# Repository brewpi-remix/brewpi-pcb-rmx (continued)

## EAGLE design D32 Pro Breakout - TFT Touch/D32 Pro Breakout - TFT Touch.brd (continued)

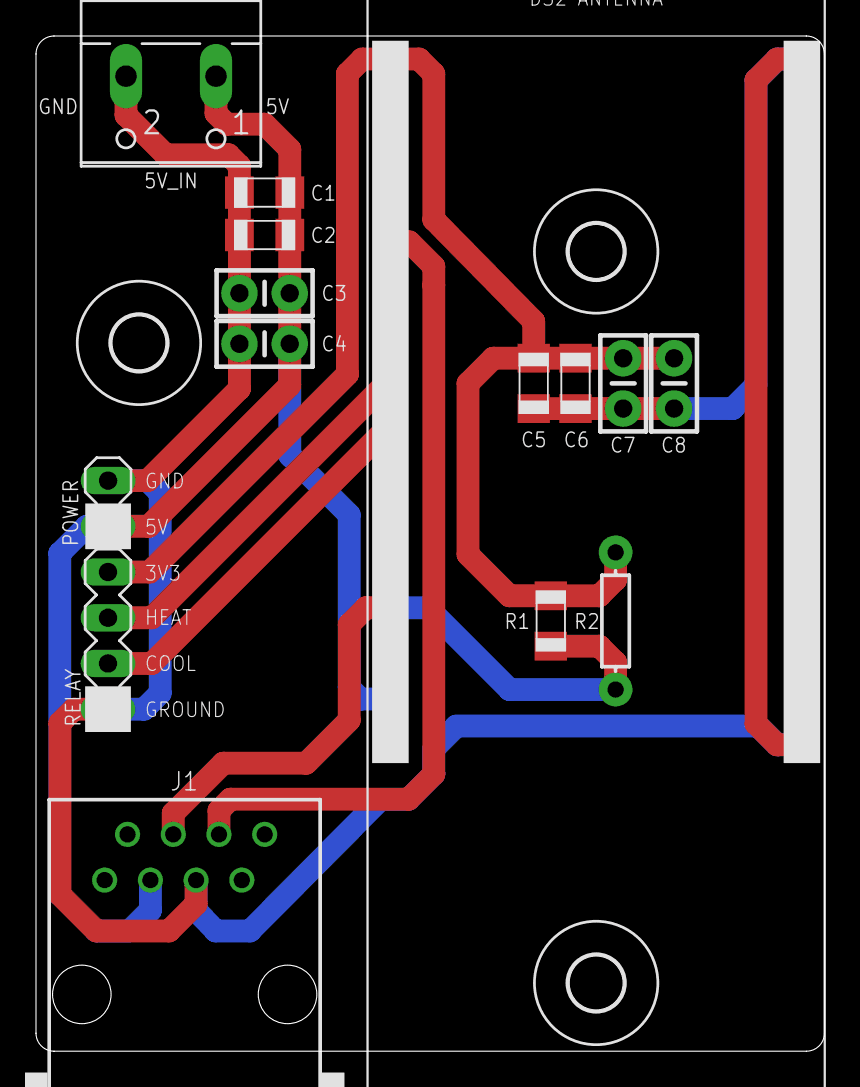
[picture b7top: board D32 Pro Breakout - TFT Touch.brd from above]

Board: 2 copper layers, 43.8 x 56.4 mm, 19 parts (1 on the bottom side), 7 nets.

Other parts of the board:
U$1, U$2, U$4: 3,0

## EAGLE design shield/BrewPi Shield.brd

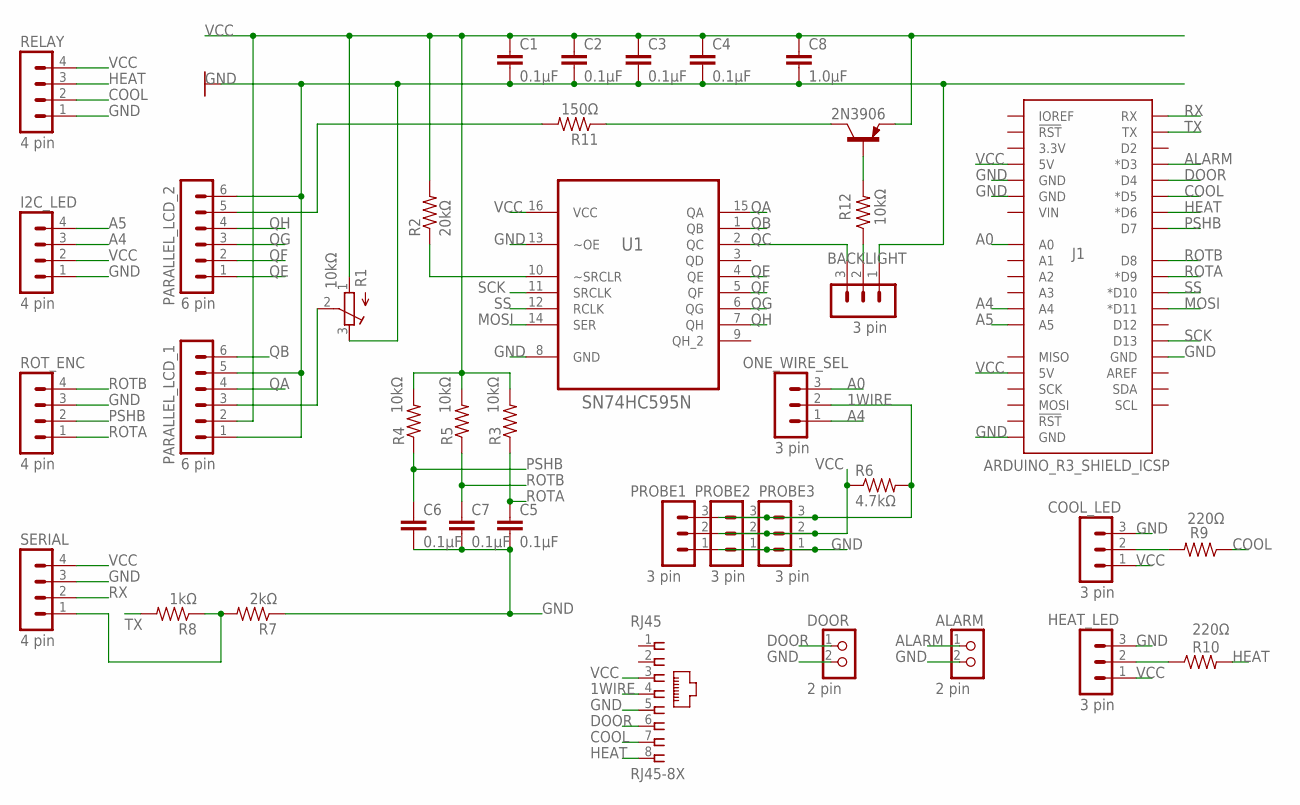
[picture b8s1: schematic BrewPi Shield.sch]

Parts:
ALARM: 2 pin; HEADER02-1
BACKLIGHT: 3 pin; HEADER03-1
C1, C2, C3, C4, C5, C6, C7: 0.1μF; CAP-PTH-SMALL-KIT
C8: 1.0μF; CAP-PTH-SMALL-KIT
COOL_LED: 3 pin; HEADER03-1
DOOR: 2 pin; HEADER02-1
HEAT_LED: 3 pin; HEADER03-1
I2C_LED: 4 pin; HEADER04-1
J1: ARDUINO_R3_SHIELD_ICSP; UNO_R3_SHIELD_ICSP
ONE_WIRE_SEL: 3 pin; HEADER03-1
PARALLEL_LCD_1, PARALLEL_LCD_2: 6 pin; HEADER06-1
PROBE1, PROBE2, PROBE3: 3 pin; HEADER03-1
Q1: 2N3906; TO92
R1: 10kΩ; RTRIM3296Y
R2: 20kΩ; AXIAL-0.3
R3, R4, R5, R12: 10kΩ; AXIAL-0.3
R6: 4.7kΩ; AXIAL-0.3
R7: 2kΩ; AXIAL-0.3
R8: 1kΩ; AXIAL-0.3
R9, R10: 220Ω; AXIAL-0.3
R11: 150Ω; AXIAL-0.3
RELAY: 4 pin; HEADER04-1
RJ45: RJ45-8X; RJ45-NO-SHIELD
ROT_ENC: 4 pin; HEADER04-1
SERIAL: 4 pin; HEADER04-1
U1: SN74HC595N; DIP254P762X508-16

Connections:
1WIRE: ONE_WIRE_SEL.2, PROBE1.3, PROBE2.3, PROBE3.3, R6.P$2 (2), RJ45.4
A0: J1.A0, ONE_WIRE_SEL.3
A4: I2C_LED.3, J1.A4, ONE_WIRE_SEL.1
A5: I2C_LED.4, J1.A5
ALARM: ALARM.1, J1.D3 (*D3)
COOL: J1.D5 (*D5), R9.P$1 (1), RELAY.2, RJ45.7
DOOR: DOOR.1, J1.D4, RJ45.6
GND: ALARM.2, BACKLIGHT.1, C1.2, C2.2, C3.2, C4.2, C5.2, C6.2, C7.2, C8.2, COOL_LED.3, DOOR.2, HEAT_LED.3, I2C_LED.1, J1.GND@0 (GND), J1.GND@1 (GND), J1.GND@2 (GND), J1.GND_ICSP (GND), PARALLEL_LCD_1.1, PARALLEL_LCD_1.5, PARALLEL_LCD_2.6, PROBE1.1, PROBE2.1, PROBE3.1, R1.3 (E), R7.P$1 (1), RELAY.1, RJ45.5, ROT_ENC.3, SERIAL.3, U1.8 (GND), U1.13 (~OE)
HEAT: J1.D6 (*D6), R10.P$2 (2), RELAY.3, RJ45.8
MOSI: J1.D11 (*D11), U1.14 (SER)
unnamed: R2.P$1 (1), U1.10 (~SRCLR)
unnamed: BACKLIGHT.2, R12.P$1 (1)
unnamed: R7.P$2 (2), R8.P$1 (1), SERIAL.1
unnamed: COOL_LED.2, R9.P$2 (2)
unnamed: PARALLEL_LCD_2.5, R11.P$2 (2)
unnamed: PARALLEL_LCD_1.3, R1.2 (S)
unnamed: Q1.1 (C), R11.P$1 (1)
unnamed: HEAT_LED.2, R10.P$1 (1)
unnamed: Q1.2 (B), R12.P$2 (2)
PSHB: C6.1, J1.D7, R4.P$1 (1), ROT_ENC.2
QA: PARALLEL_LCD_1.4, U1.15 (QA)
QB: PARALLEL_LCD_1.6, U1.1 (QB)
QC: BACKLIGHT.3, U1.2 (QC)
QE: PARALLEL_LCD_2.1, U1.4 (QE)
QF: PARALLEL_LCD_2.2, U1.5 (QF)
QG: PARALLEL_LCD_2.3, U1.6 (QG)
QH: PARALLEL_LCD_2.4, U1.7 (QH)
ROTA: C5.1, J1.D9 (*D9), R3.P$1 (1), ROT_ENC.1
ROTB: C7.1, J1.D8, R5.P$1 (1), ROT_ENC.4
RX: J1.RX, SERIAL.2
SCK: J1.D13, U1.11 (SRCLK)
SS: J1.D10 (*D10), U1.12 (RCLK)
TX: J1.TX, R8.P$2 (2)
VCC: C1.1, C2.1, C3.1, C4.1, C8.1, COOL_LED.1, HEAT_LED.1, I2C_LED.2, J1.5V, J1.5V_ICSP (5V), PARALLEL_LCD_1.2, PROBE1.2, PROBE2.2, PROBE3.2, Q1.3 (E), R1.1 (A), R2.P$2 (2), R3.P$2 (2), R4.P$2 (2), R5.P$2 (2), R6.P$1 (1), RELAY.4, RJ45.3, SERIAL.4, U1.16 (VCC)

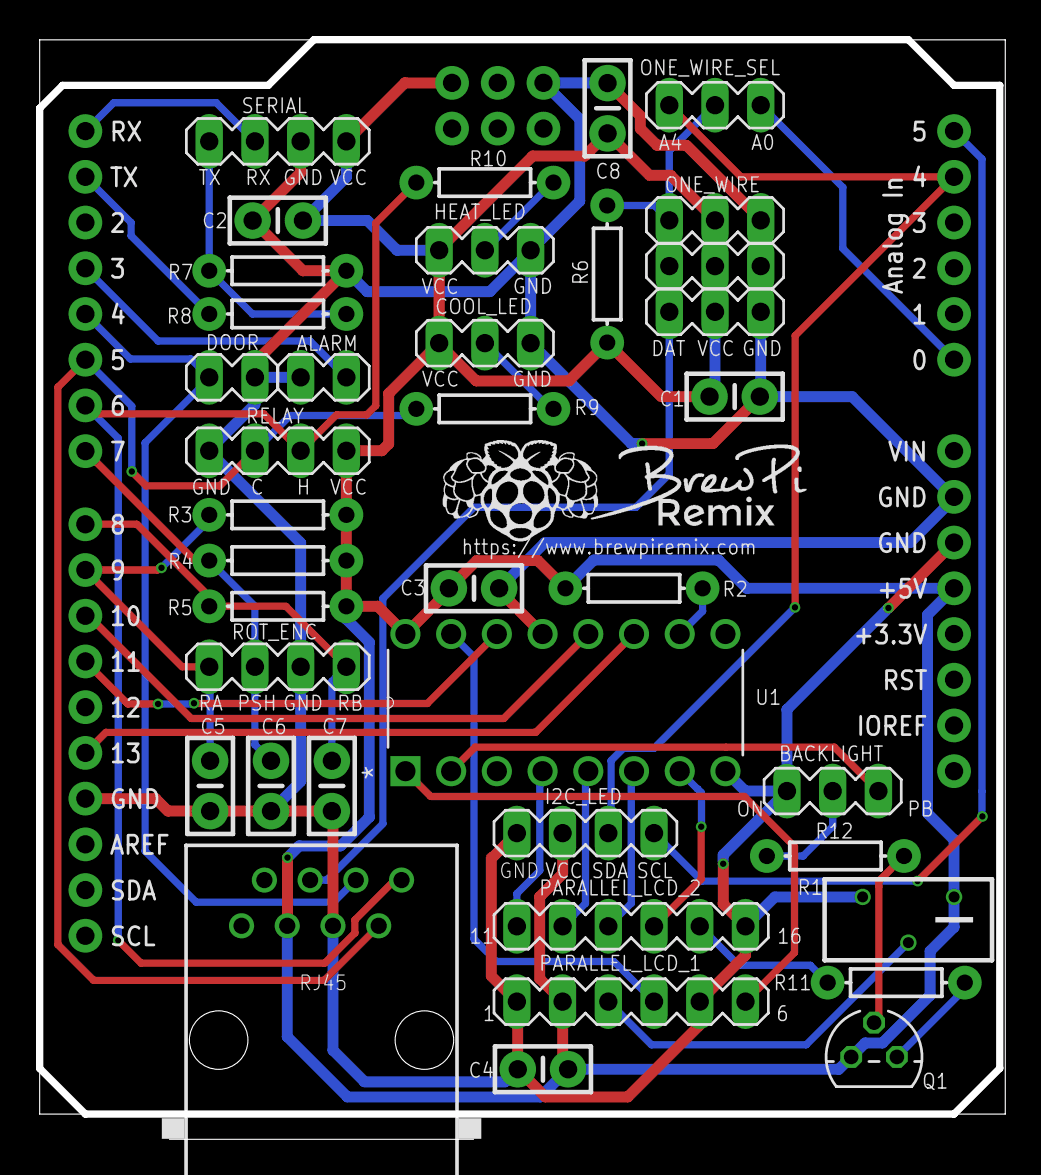
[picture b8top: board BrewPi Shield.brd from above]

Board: 2 copper layers, 53.6 x 61.1 mm, 39 parts (0 on the bottom side), 34 nets.

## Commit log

2019-06-23 Legacy 1.1 boards
2019-06-23 Updated included files
2019-06-23 Rename to versionless names
2019-06-23 Rename shield directory
2019-06-23 Added CHANGELOG
2019-06-23 Version 1.2 upload
2019-06-23 Initial upload
2019-06-23 Version 1.3 upload
2019-06-23 Version 1.3.1 upload
2019-06-23 Moved traces and silkscreens
2019-06-30 Update logo
2019-06-30 Update logo, remove acid trap
2019-06-30 Update CHANGELOGs
2019-06-30 Add labels for LEDs
2019-06-30 Update links
2019-06-30 Add README
2019-06-30 Add images
2019-06-30 Reduce image size
2019-11-10 Add ESP8266 shield
2019-11-18 Remove 90deg connection at power
2019-11-18 Update link and images
2019-11-18 Change to pcbs.io link
2019-11-18 Fix typo
2019-11-18 Update to pcbs.io images
2019-11-18 Change all links to pcbs.io
2019-11-18 Remove a bunch of 90's
2019-11-18 Update pours
2019-11-30 New board for D32 Pro
2019-11-30 Update D1, rename dirs
2019-11-30 Add RJ45 Sensor Breakout
2019-11-30 Add BOMs
2019-12-01 Rename, add GND to mounting ears
2019-12-01 Add grounds to the shield
2019-12-01 Updated part
2019-12-02 Update README's images and links
2019-12-02 Script for logo added
2020-05-22 Silk for pins was reversed
2020-05-22 Rename folders
2020-05-22 Update folder hierarchy
2020-05-22 Update graphic
2020-05-22 Wrong license was applied
2020-05-22 Proper license
2020-11-09 Add RJ45 Breakout
2021-03-15 Reorganize and add I2C shield
2021-03-15 Add voltage select header
2021-03-16 Fix pour and links
2021-05-30 Add links to pre-built splitters
2024-10-19 Handle OS LF differences
2024-10-19 Ignore MacOS file
2024-10-19 Add schematic
2024-10-19 Add more info for I2C shield variant
2024-10-19 Remove PCB.io link
